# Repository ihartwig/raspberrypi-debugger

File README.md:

Raspberry Pi Debugger
=====================

This repository houses bare-metal hardware debugging tools for Raspberry Pi.

</img>

## Features

* JTAG, UART, and power for RPi on single USB interface
* Supports Pi 0, 1 (Rev 2), 1+, 2 by breaking away the top section of the board when used with a Pi 1.
* Power control of RPi for system reset from UART (DTR), JTAG (sRST), and physical button
* Does not explode if RPi is powered directly (backpowering the debugger board) or both are powered at the same time independently
* Current measuring by shunt on the RPi 5V supply
* RPi HAT EEPROM footprints available but not populated
* Top SMD only design using the [RPi Foundation example SMT header](https://www.raspberrypi.org/blog/introducing-raspberry-pi-hats/) (optionally can use through hole header soldered later)

## Development Structure

* **config**: configurations for FT_Prog, OpenOCD, and GDB
* **docs**: datasheets and reference schematics this board is based on.
* **debugger**: rev 1 schematic and board in eagle
* **debugger2**: rev 2+ schematic and board in kicad
* **RPiDebuggerVCPBlock**: OS X kernel extension to allow using JTAG with serial

## Support Software

Windows and OS X users need to install the [FTDI VCP drivers](http://www.ftdichip.com/Drivers/VCP.htm). Windows may install it automatically. Linux users can use either the built or FTDI drivers. OS X (10.9+) has basic support for serial with the built in driver but does not trigger the DTR line used to control RPi power.

On OS X the VCP driver will try to assign a serial port to the FTDI channel we want to use for JTAG, preventing us from using JTAG and serial at the same time. We can fix this by installing a dummy kernel module ([suggested resolution from Apple](https://developer.apple.com/library/mac/technotes/tn2315/_index.html)), RPiDebuggerVCPBlock. Download the kext from the [relase page](https://github.com/ihartwig/raspberrypi-debugger/releases) and place it in `/Library/Extensions`. Since the kext is not signed, you must [disable kext certificate checking](http://apple.stackexchange.com/questions/163059/how-can-i-disable-kext-signing-in-mac-os-x-10-10-yosemite) in 10.10+.

To use JTAG on the RPi you need to enable the alternate pin functions in software. This can be done easily by loading the SD card with a dummy kernel that enables the JTAG interface on boot and waits.

## FTDI EEPROM

Newly assembled boards with a blank eeprom should be programmed. Functionally, this tells the windows driver to not open a com port on the FTDI channel we use for JTAG. The templates under `config` can be programmed with [FT_Prog](http://www.ftdichip.com/Support/Utilities.htm#FT_PROG).

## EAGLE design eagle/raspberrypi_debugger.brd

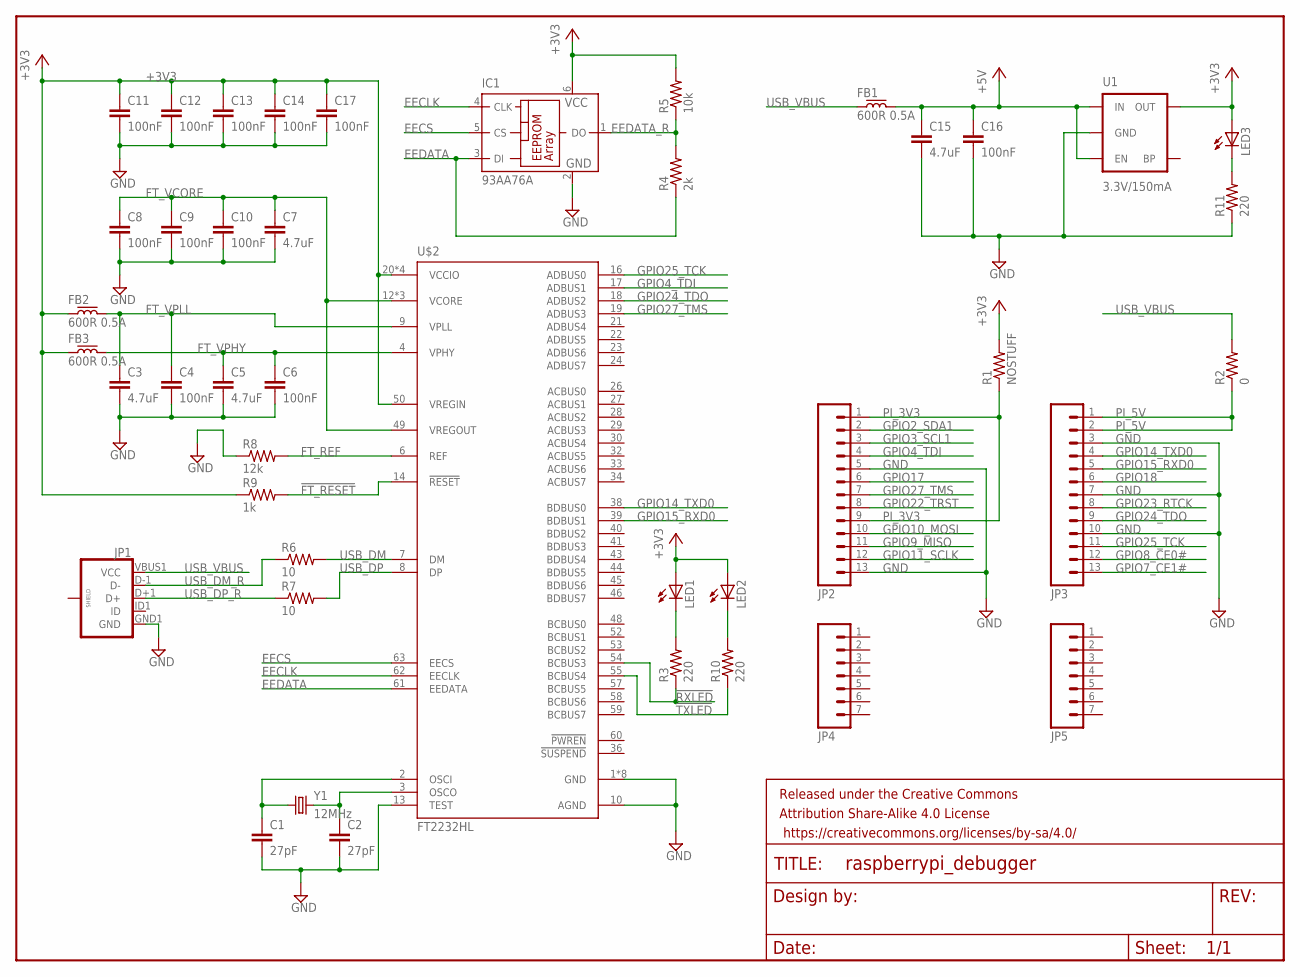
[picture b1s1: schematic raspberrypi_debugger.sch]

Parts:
C1, C2: 27pF; C0805
C3, C5, C7, C15: 4.7uF; C1206
C4, C6, C8, C9, C10, C11, C12, C13, C14, C16, C17: 100nF; C0805
FB1, FB2, FB3: 600R 0.5A; R0805
FRAME1: FRAME-LETTERNO_PACKAGE; DUMMY
IC1: 93AA76A; SOT23-6
JP1: USB_MICROB_PLUGCONN-11752; USB-B-MICRO-SMD_V03
JP2, JP3: M13LOCK; 1X13_LOCK
JP4, JP5: M07LOCK; 1X07_LOCK
LED1, LED2, LED3: LEDCHIP-LED0805; CHIP-LED0805
R1: NOSTUFF; R0805
R2: 0; R0805
R3, R10, R11: 220; R0805
R4: 2k; R0805
R5: 10k; R0805
R6, R7: 10; R0805
R8: 12k; R0805
R9: 1k; R0805
U1: 3.3V/150mA; SOT23-5
U$2: FT2232HL; TQFP64-10X10
Y1: 12MHz; HC49UP

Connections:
!FT_RESET: R9.2, U$2.14 (!RESET)
!RXLED: R3.1, U$2.54 (BCBUS3)
!TXLED: R10.1, U$2.55 (BCBUS4)
+3V3: C11.1, C12.1, C13.1, C14.1, C17.1, FB2.2, FB3.2, IC1.6 (VCC), LED1.A, LED2.A, LED3.A, R1.2, R5.2, R9.1, U1.5 (OUT), U$2.20 (VCCIO), U$2.31 (VCCIO), U$2.42 (VCCIO), U$2.50 (VREGIN), U$2.56 (VCCIO)
+5V: C15.1, C16.1, FB1.1, U1.1 (IN), U1.3 (EN)
EECLK: IC1.4 (CLK), U$2.62 (EECLK)
EECS: IC1.5 (CS), U$2.63 (EECS)
EEDATA: IC1.3 (DI), R4.1, U$2.61 (EEDATA)
EEDATA_R: IC1.1 (DO), R4.2, R5.1
FT_REF: R8.2, U$2.6 (REF)
FT_VCORE: C7.1, C8.1, C9.1, C10.1, U$2.12 (VCORE), U$2.37 (VCORE), U$2.49 (VREGOUT), U$2.64 (VCORE)
FT_VPHY: C5.1, C6.1, FB3.1, U$2.4 (VPHY)
FT_VPLL: C3.1, C4.1, FB2.1, U$2.9 (VPLL)
GND: C1.2, C2.2, C3.2, C4.2, C5.2, C6.2, C7.2, C8.2, C9.2, C10.2, C11.2, C12.2, C13.2, C14.2, C15.2, C16.2, C17.2, IC1.2 (GND), JP1.GND1 (GND), JP2.5, JP2.13, JP3.3, JP3.7, JP3.10, R8.1, R11.1, U1.2 (GND), U$2.1 (GND), U$2.5 (GND), U$2.10 (AGND), U$2.11 (GND), U$2.13 (TEST), U$2.15 (GND), U$2.25 (GND), U$2.35 (GND), U$2.47 (GND), U$2.51 (GND)
GPIO2_SDA1: JP2.2
GPIO3_SCL1: JP2.3
GPIO4_TDI: JP2.4, U$2.17 (ADBUS1)
GPIO7_CE1#: JP3.13
GPIO8_CE0#: JP3.12
GPIO9_MISO: JP2.11
GPIO10_MOSI: JP2.10
GPIO11_SCLK: JP2.12
GPIO14_TXD0: JP3.4, U$2.38 (BDBUS0)
GPIO15_RXD0: JP3.5, U$2.39 (BDBUS1)
GPIO17: JP2.6
GPIO18: JP3.6
GPIO22_TRST: JP2.8
GPIO23_RTCK: JP3.8
GPIO24_TDO: JP3.9, U$2.18 (ADBUS2)
GPIO25_TCK: JP3.11, U$2.16 (ADBUS0)
GPIO27_TMS: JP2.7, U$2.19 (ADBUS3)
unnamed: C1.1, U$2.2 (OSCI), Y1.1
unnamed: C2.1, U$2.3 (OSCO), Y1.2
unnamed: LED1.C, R3.2
unnamed: LED2.C, R10.2
unnamed: LED3.C, R11.2
PI_3V3: JP2.1, JP2.9, R1.1
PI_5V: JP3.1, JP3.2, R2.1
USB_DM: R6.2, U$2.7 (DM)
USB_DM_R: JP1.D-1 (D-), R6.1
USB_DP: R7.2, U$2.8 (DP)
USB_DP_R: JP1.D+1 (D+), R7.1
USB_VBUS: FB1.2, JP1.VBUS1 (VCC), R2.2

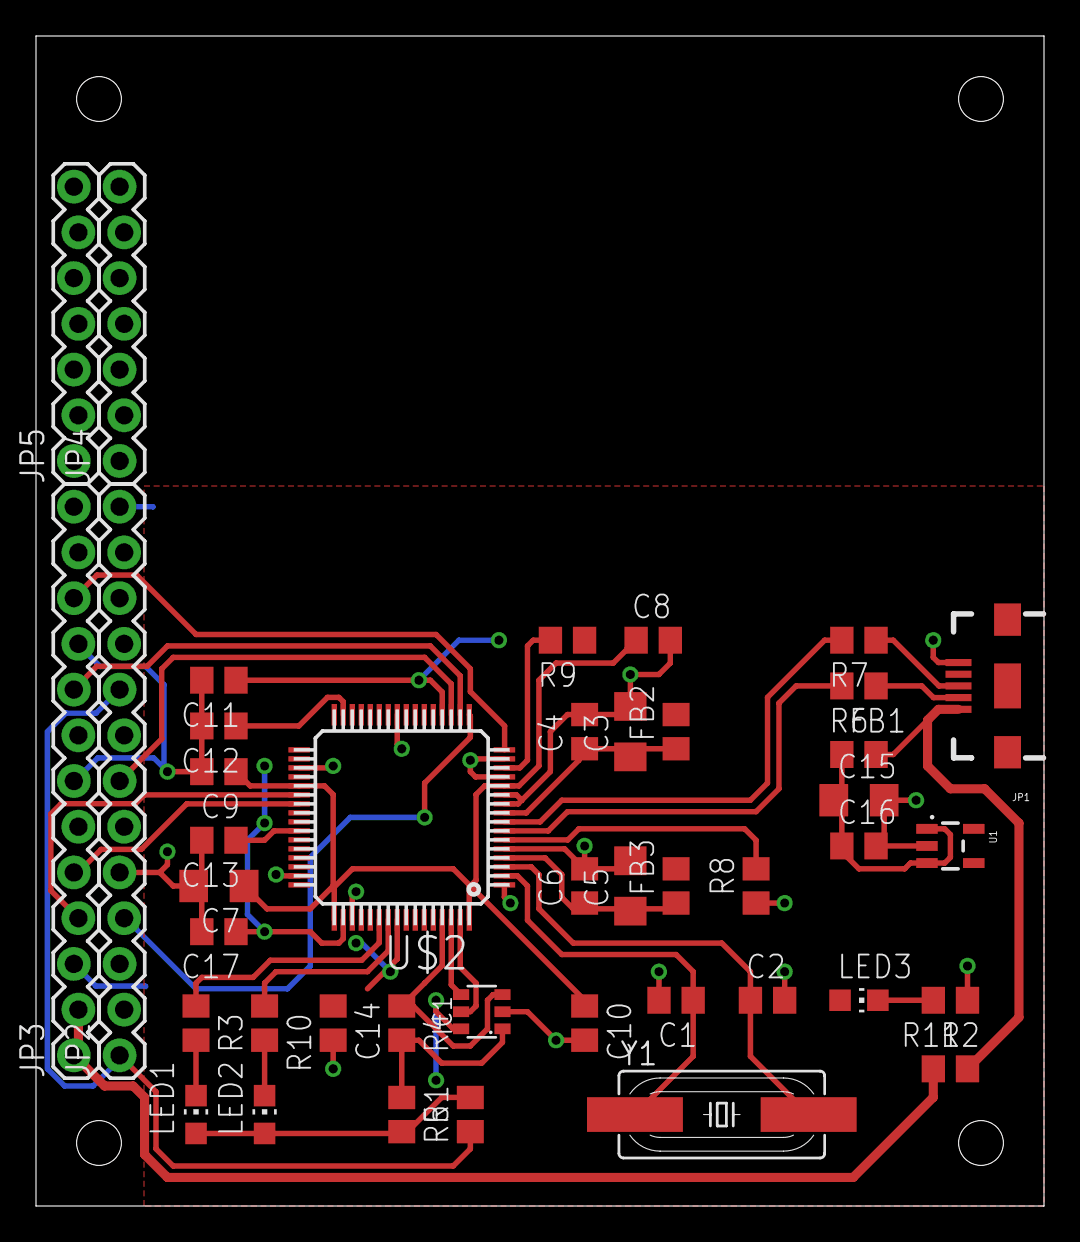
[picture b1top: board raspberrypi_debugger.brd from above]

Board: 2 copper layers, 56.0 x 65.0 mm, 44 parts (0 on the bottom side), 32 nets.

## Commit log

2016-01-27 initial schematic and routing for Pi 1, 2
2016-01-27 add readme
2016-02-01 schematic and routing for debugger2
2016-02-02 update board layout for 6/6mil (was 5/5mil)
2016-02-02 add debugger2 gerbers
2016-02-02 add debugger2 schematic in pdf
2016-03-16 add license
2016-03-16 update bom information
2016-04-30 rev 2.1 fixes for UART, JTAG resets, EEPROM packages
    * fix UART (FTDI Ch B) RX/TX backwards
    * fix GPIO22_TRST floating by connecting to FTDI Ch A. in debugger 1 we pulled up to 3.3V, but this gives us software control of tap reset
    * add options to control RPi power (reset) from FTDI Ch A and button. diodes can be left off BOM to disable a source
    * add external drain resistor for vbus switch (backpowering from rpi can cause fet drain in the switch to magic smoke)
    * add grounding pad for probe clips
    * make holes floating so we can use metal standoffs
2016-05-06 rev 2.1.1 swap usb micro b to SMT version since many board houses can't make the slots
2016-05-12 rename eagle to debugger to reflect first generation hardware
2016-05-24 add RPiDebuggerVCPBlock kernel extension v1.0
2016-05-24 update readme with build and installation info
2016-07-11 rev 2.1.2 swap tantalum caps for ceramic, 2:1 aspect vias
2016-07-13 rev 2.1.3 combine P1 and P2, update BOM, make R3 possible value
2016-07-18 change shunt resistor to 0.05 ohm
2016-08-11 swap rpi connector for no paste verison and no stuff
2016-08-11 fix missing Y1 in position file by adding INSERT footprint attribute
2016-10-19 update U2 and U3 part no on bom and schematic. prevents U2 smoking
2016-10-26 fix D4 D5 part in bom for mismatched footprint, change sch paper size so we plot everything
2017-11-24 Update LICENSE

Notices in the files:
parts and their libraries:
SparkFun-Connectors: Licensing: Creative Commons ShareAlike 4.0 International - https://creativecommons.org/licenses/by-sa/4.0
SparkFun-Aesthetics: Released under the Creative Commons Attribution Share-Alike 4.0 License
SparkFun-Aesthetics: https://creativecommons.org/licenses/by-sa/4.0
